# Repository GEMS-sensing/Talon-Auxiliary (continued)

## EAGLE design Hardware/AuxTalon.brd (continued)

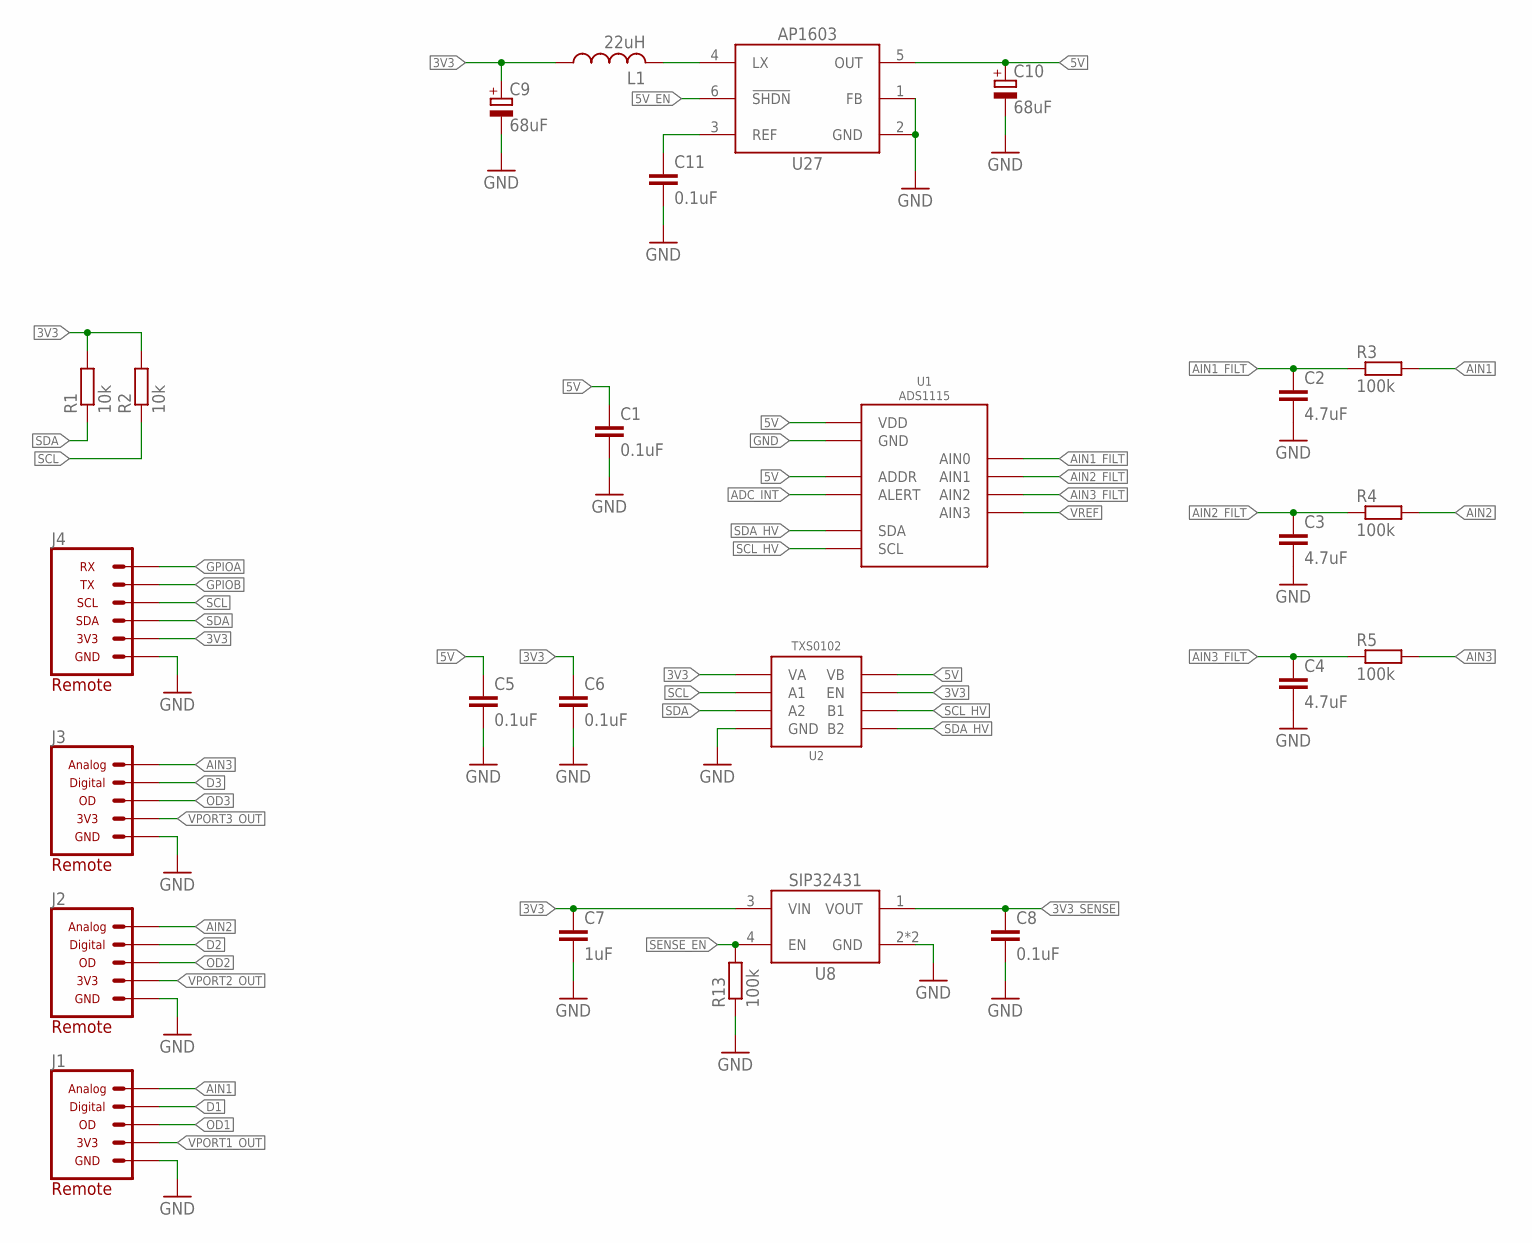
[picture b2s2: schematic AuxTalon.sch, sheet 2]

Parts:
C1, C5, C6, C8, C11: 0.1uF; C0402
C2, C3, C4: 4.7uF; C0805
C7: 1uF; C0603
C9, C10: 68uF; 153CLV-0605
J1, J2, J3: CONN_AUX_M12_REMOTE; 1X05_M12_TE_T41410
J4: CONN_TALON_REMOTE; 1X06_MICROLOCKPLUS
L1: 22uH; WE-TPC(3.8X3.8)
R1, R2: 10k; R0402
R3, R4, R5, R13: 100k; R0402
U1: ADS1115; VSSOP_10
U2: TXS0102DCU; DCU_(R-PDSO-G8)
U8: SIP32431TDFN; TDFN_4
U27: AP1603; TSOT23-6_DDC

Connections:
3V3: C6.1, C7.1, C9.+, J4.5 (3V3), L1.1, R1.2, R2.2, U2.3 (VA), U2.6 (EN), U8.3 (VIN); also elsewhere on the board
3V3_SENSE: C8.1, U8.1 (VOUT); also elsewhere on the board
5V: C1.1, C5.1, C10.+, U1.1 (ADDR), U1.8 (VDD), U2.7 (VB), U27.5 (OUT); also elsewhere on the board
5V_EN: U27.6 (!SHDN); also elsewhere on the board
ADC_INT: U1.2 (ALERT)
AIN1: J1.4 (ANALOG), R3.2
AIN1_FILT: C2.1, R3.1, U1.4 (AIN0)
AIN2: J2.4 (ANALOG), R4.2
AIN2_FILT: C3.1, R4.1, U1.5 (AIN1)
AIN3: J3.4 (ANALOG), R5.2
AIN3_FILT: C4.1, R5.1, U1.6 (AIN2)
D1: J1.5 (DIGITAL); also elsewhere on the board
D2: J2.5 (DIGITAL); also elsewhere on the board
D3: J3.5 (DIGITAL); also elsewhere on the board
GND: C1.2, C2.2, C3.2, C4.2, C5.2, C6.2, C7.2, C8.2, C9.-, C10.-, C11.2, J1.3 (GND), J2.3 (GND), J3.3 (GND), J4.6 (GND), R13.1, U1.3 (GND), U2.2 (GND), U8.2 (GND), U8.EP (GND), U27.1 (FB), U27.2 (GND); also elsewhere on the board
GPIOA: J4.1 (RX); also elsewhere on the board
GPIOB: J4.2 (TX); also elsewhere on the board
unnamed: C11.1, U27.3 (REF)
unnamed: L1.2, U27.4 (LX)
OD1: J1.2 (DIGITAL_OPENDRAIN); also elsewhere on the board
OD2: J2.2 (DIGITAL_OPENDRAIN); also elsewhere on the board
OD3: J3.2 (DIGITAL_OPENDRAIN); also elsewhere on the board
SCL: J4.3 (SCL), R2.1, U2.5 (A1); also elsewhere on the board
SCL_HV: U1.10 (SCL), U2.8 (B1)
SDA: J4.4 (SDA), R1.1, U2.4 (A2); also elsewhere on the board
SDA_HV: U1.9 (SDA), U2.1 (B2)
SENSE_EN: R13.2, U8.4 (EN); also elsewhere on the board
VPORT1_OUT: J1.1 (3V3); also elsewhere on the board
VPORT2_OUT: J2.1 (3V3); also elsewhere on the board
VPORT3_OUT: J3.1 (3V3); also elsewhere on the board
VREF: U1.7 (AIN3); also elsewhere on the board

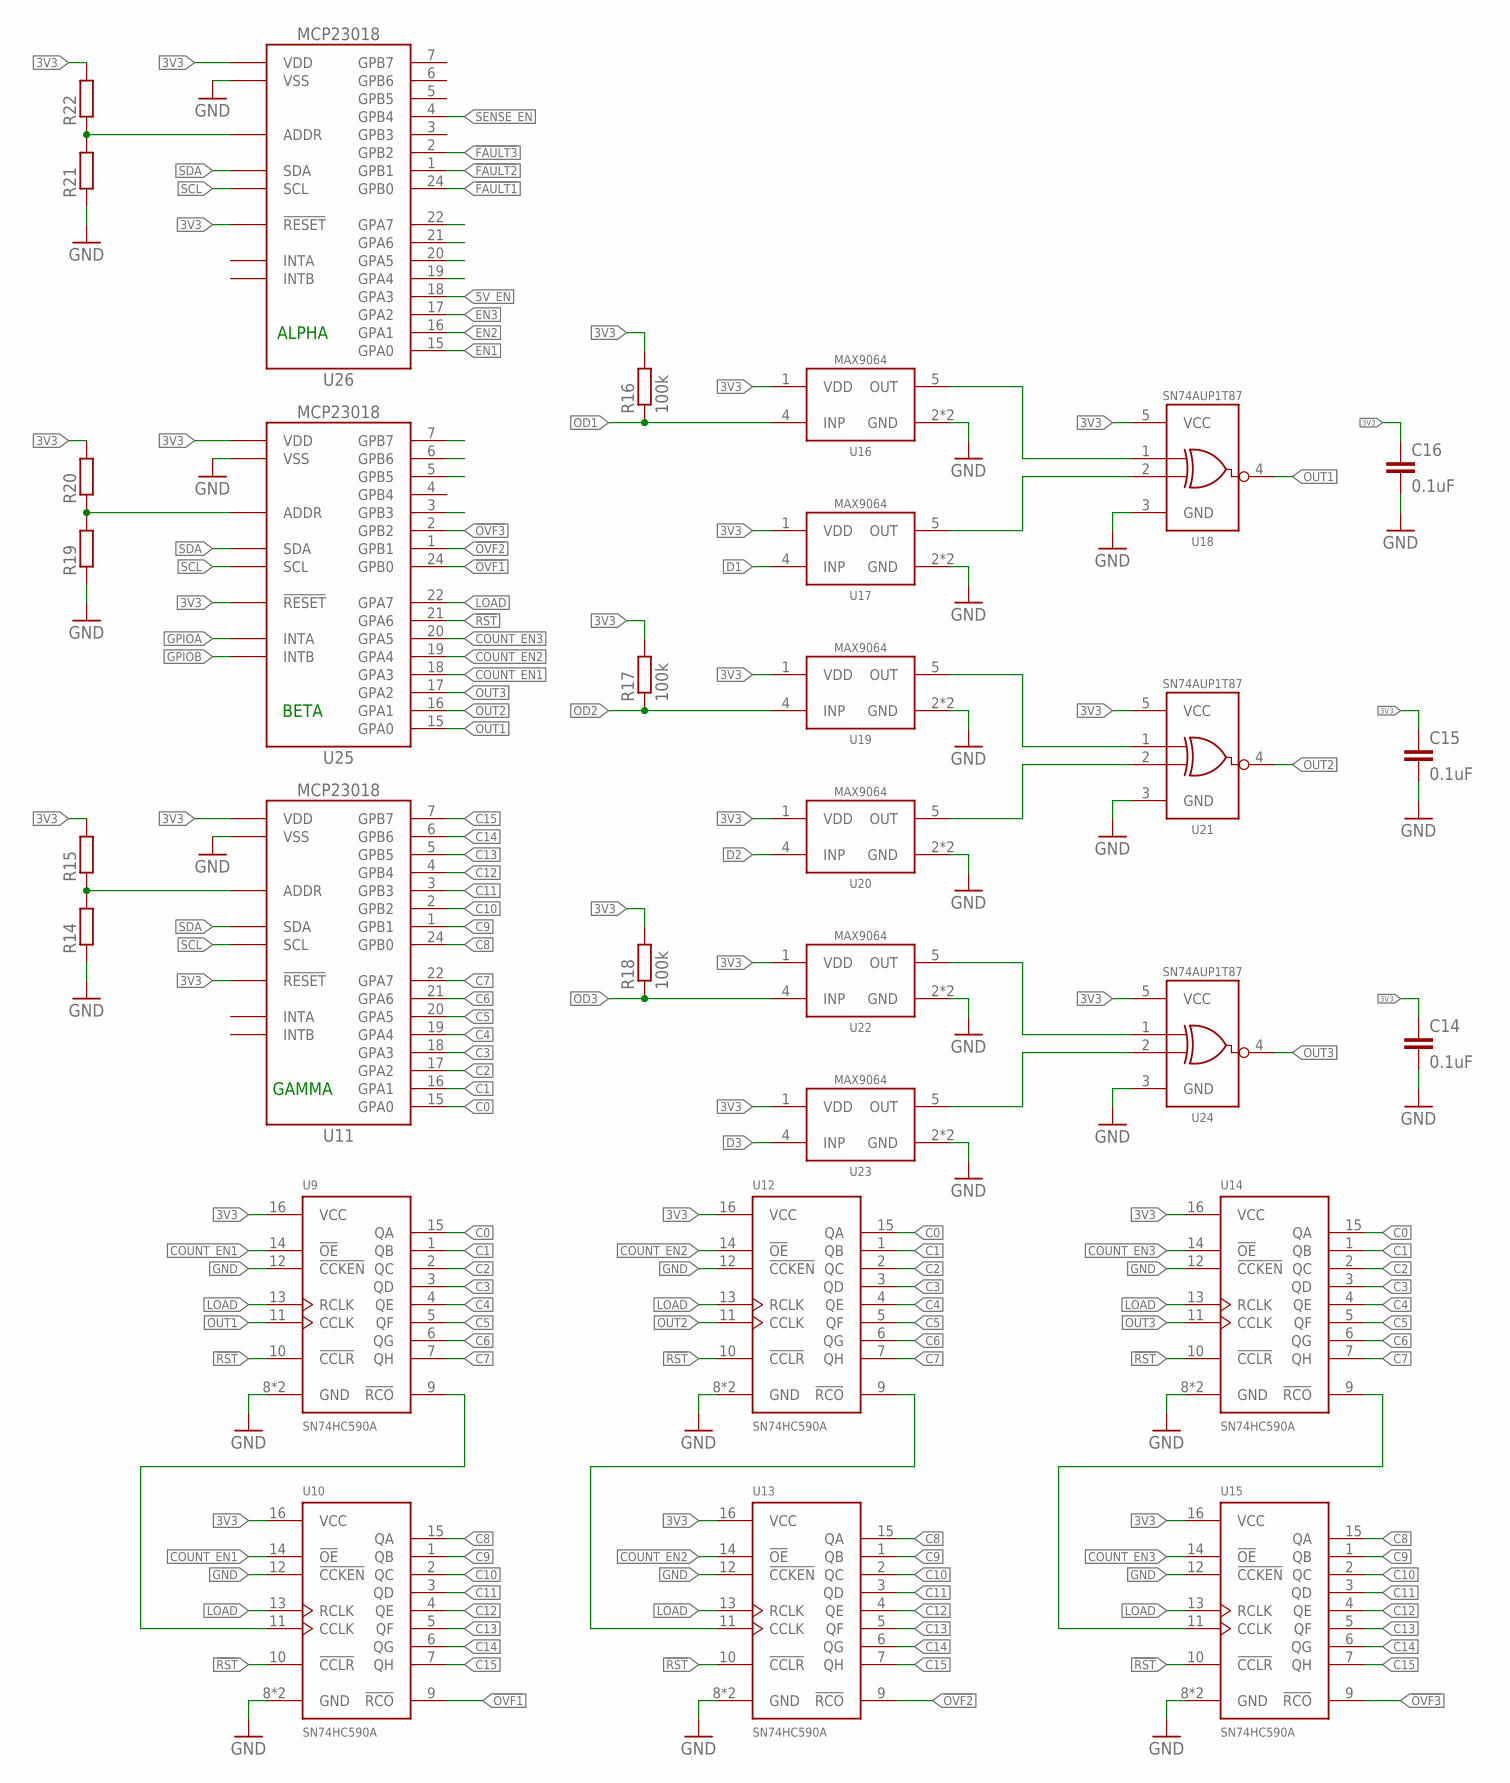
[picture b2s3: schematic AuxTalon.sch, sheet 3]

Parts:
C14, C15, C16: 0.1uF; C0402
R14, R15, R19, R20, R21, R22: R-EU_R0603; R0603
R16, R17, R18: 100k; R0402
U9, U10, U12, U13, U14, U15: SN74HC590AVQFN; VQFN-16
U11, U25, U26: MCP23018QFN; QFN24
U16, U17, U19, U20, U22, U23: MAX9064; SOT23-5
U18, U21, U24: SN74AUP1T87; DCK_R-PDSO-G5

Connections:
3V3: C14.1, C15.1, C16.1, R15.2, R16.2, R17.2, R18.2, R20.2, R22.2, U9.16 (VCC), U10.16 (VCC), U11.8 (VDD), U11.12 (!RESET), U12.16 (VCC), U13.16 (VCC), U14.16 (VCC), U15.16 (VCC), U16.1 (VDD), U17.1 (VDD), U18.5 (VCC), U19.1 (VDD), U20.1 (VDD), U21.5 (VCC), U22.1 (VDD), U23.1 (VDD), U24.5 (VCC), U25.8 (VDD), U25.12 (!RESET), U26.8 (VDD), U26.12 (!RESET); also elsewhere on the board
5V_EN: U26.18 (GPA3); also elsewhere on the board
!FAULT1: U26.24 (GPB0); also elsewhere on the board
!FAULT2: U26.1 (GPB1); also elsewhere on the board
!FAULT3: U26.2 (GPB2); also elsewhere on the board
!OVF1: U10.9 (!RCO), U25.24 (GPB0)
!OVF2: U13.9 (!RCO), U25.1 (GPB1)
!OVF3: U15.9 (!RCO), U25.2 (GPB2)
!RST: U9.10 (!CCLR), U10.10 (!CCLR), U12.10 (!CCLR), U13.10 (!CCLR), U14.10 (!CCLR), U15.10 (!CCLR), U25.21 (GPA6)
C0: U9.15 (QA), U11.15 (GPA0), U12.15 (QA), U14.15 (QA)
C1: U9.1 (QB), U11.16 (GPA1), U12.1 (QB), U14.1 (QB)
C2: U9.2 (QC), U11.17 (GPA2), U12.2 (QC), U14.2 (QC)
C3: U9.3 (QD), U11.18 (GPA3), U12.3 (QD), U14.3 (QD)
C4: U9.4 (QE), U11.19 (GPA4), U12.4 (QE), U14.4 (QE)
C5: U9.5 (QF), U11.20 (GPA5), U12.5 (QF), U14.5 (QF)
C6: U9.6 (QG), U11.21 (GPA6), U12.6 (QG), U14.6 (QG)
C7: U9.7 (QH), U11.22 (GPA7), U12.7 (QH), U14.7 (QH)
C8: U10.15 (QA), U11.24 (GPB0), U13.15 (QA), U15.15 (QA)
C9: U10.1 (QB), U11.1 (GPB1), U13.1 (QB), U15.1 (QB)
C10: U10.2 (QC), U11.2 (GPB2), U13.2 (QC), U15.2 (QC)
C11: U10.3 (QD), U11.3 (GPB3), U13.3 (QD), U15.3 (QD)
C12: U10.4 (QE), U11.4 (GPB4), U13.4 (QE), U15.4 (QE)
C13: U10.5 (QF), U11.5 (GPB5), U13.5 (QF), U15.5 (QF)
C14: U10.6 (QG), U11.6 (GPB6), U13.6 (QG), U15.6 (QG)
C15: U10.7 (QH), U11.7 (GPB7), U13.7 (QH), U15.7 (QH)
COUNT_EN1: U9.14 (!OE), U10.14 (!OE), U25.18 (GPA3)
COUNT_EN2: U12.14 (!OE), U13.14 (!OE), U25.19 (GPA4)
COUNT_EN3: U14.14 (!OE), U15.14 (!OE), U25.20 (GPA5)
D1: U17.4 (INP); also elsewhere on the board
D2: U20.4 (INP); also elsewhere on the board
D3: U23.4 (INP); also elsewhere on the board
EN1: U26.15 (GPA0); also elsewhere on the board
EN2: U26.16 (GPA1); also elsewhere on the board
EN3: U26.17 (GPA2); also elsewhere on the board
GND: C14.2, C15.2, C16.2, R14.1, R19.1, R21.1, U9.8 (GND), U9.12 (!CCKEN), U9.EP (GND), U10.8 (GND), U10.12 (!CCKEN), U10.EP (GND), U11.23 (VSS), U11.EP (VSS), U12.8 (GND), U12.12 (!CCKEN), U12.EP (GND), U13.8 (GND), U13.12 (!CCKEN), U13.EP (GND), U14.8 (GND), U14.12 (!CCKEN), U14.EP (GND), U15.8 (GND), U15.12 (!CCKEN), U15.EP (GND), U16.2 (GND), U16.3 (GND), U17.2 (GND), U17.3 (GND), U18.3 (GND), U19.2 (GND), U19.3 (GND), U20.2 (GND), U20.3 (GND), U21.3 (GND), U22.2 (GND), U22.3 (GND), U23.2 (GND), U23.3 (GND), U24.3 (GND), U25.23 (VSS), U25.EP (VSS), U26.23 (VSS), U26.EP (VSS); also elsewhere on the board
GPIOA: U25.14 (INTA); also elsewhere on the board
GPIOB: U25.13 (INTB); also elsewhere on the board
LOAD: U9.13 (RCLK), U10.13 (RCLK), U12.13 (RCLK), U13.13 (RCLK), U14.13 (RCLK), U15.13 (RCLK), U25.22 (GPA7)
MUX_SEL2: U25.5 (GPB5); also elsewhere on the board
unnamed: U9.9 (!RCO), U10.11 (CCLK)
unnamed: U12.9 (!RCO), U13.11 (CCLK)
unnamed: U14.9 (!RCO), U15.11 (CCLK)
unnamed: R14.2, R15.1, U11.11 (ADDR)
unnamed: U20.5 (OUT), U21.2 (B)
unnamed: U19.5 (OUT), U21.1 (A)
unnamed: U16.5 (OUT), U18.1 (A)
unnamed: U17.5 (OUT), U18.2 (B)
unnamed: U23.5 (OUT), U24.2 (B)
unnamed: U22.5 (OUT), U24.1 (A)
unnamed: R21.2, R22.1, U26.11 (ADDR)
unnamed: R19.2, R20.1, U25.11 (ADDR)
OD1: R16.1, U16.4 (INP); also elsewhere on the board
OD2: R17.1, U19.4 (INP); also elsewhere on the board
OD3: R18.1, U22.4 (INP); also elsewhere on the board
OUT1: U9.11 (CCLK), U18.4 (Y), U25.15 (GPA0)
OUT2: U12.11 (CCLK), U21.4 (Y), U25.16 (GPA1)
OUT3: U14.11 (CCLK), U24.4 (Y), U25.17 (GPA2)
SCL: U11.9 (SCL), U25.9 (SCL), U26.9 (SCL); also elsewhere on the board
SDA: U11.10 (SDA), U25.10 (SDA), U26.10 (SDA); also elsewhere on the board
SENSE_EN: U26.4 (GPB4); also elsewhere on the board

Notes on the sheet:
BETA
GAMMA
ALPHA

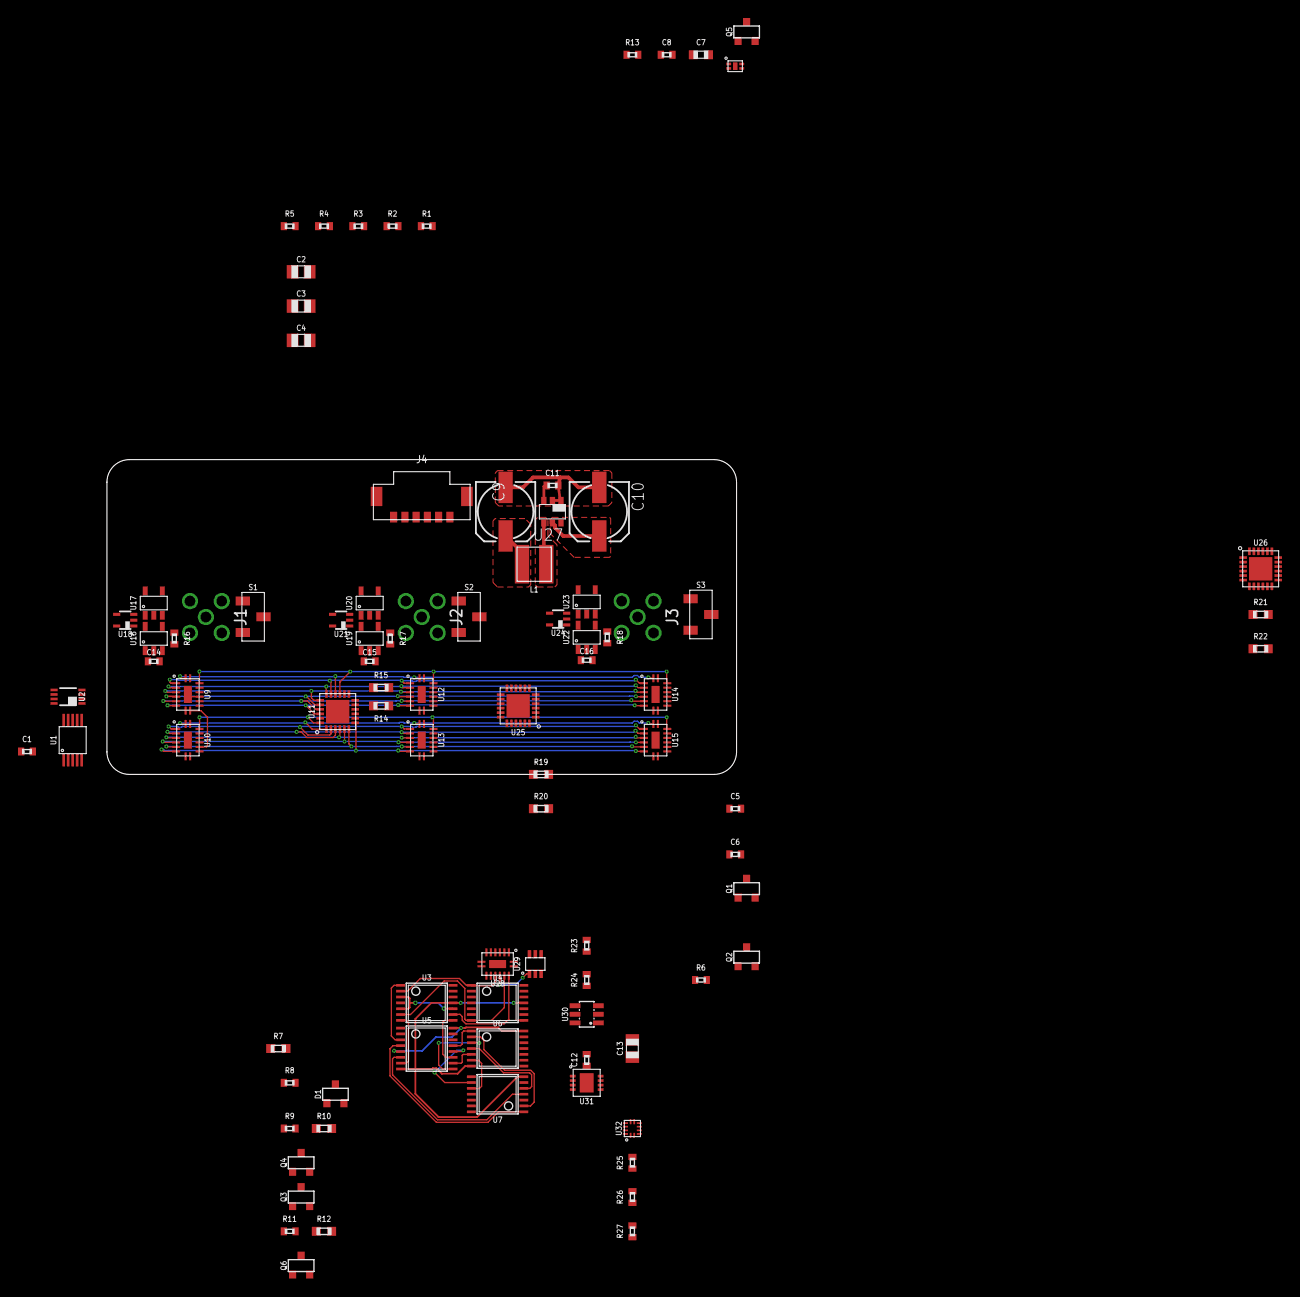
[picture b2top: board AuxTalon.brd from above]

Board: 2 copper layers, 70.0 x 35.0 mm, 90 parts (0 on the bottom side), 107 nets.

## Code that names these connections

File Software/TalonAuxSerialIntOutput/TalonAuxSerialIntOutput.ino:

#include <Wire.h>
#include <Arduino.h>
#include <MCP23018.h>

// #define OVERFLOW_ONLY 

//Input Pins
const uint8_t GPIOA = 5;
const uint8_t GPIOB = 6;

//IO Expander Pins - ALPHA
const uint8_t REG_EN = 7;
const uint8_t ADC_INT = 6;

//IO Expander Pins - BETA
const uint8_t LOAD = 7;
const uint8_t RST = 6;
const uint8_t OUT1 = 0;
// const uint8_t COUNT_EN3 = 5;
// const uint8_t COUNT_EN2 = 4;
const uint8_t COUNT_EN1 = 3;
const uint8_t OVF1 = 8;

//Configured for pins on the Particle Boron
//const uint8_t EXT_EN = 8;
//const uint8_t SDA_CTRL = 2;

const uint8_t EXT_EN = 13;
const uint8_t SDA_CTRL = 5;

volatile bool OverflowFlags[3] = {0}; //Set by OverflowISR, cleared in main loop
volatile bool EventFlags[3] = {0}; //Set by EventISR, cleared in main loop

volatile bool NewOverflow = false; //Used to indicate a new overflow condition
volatile bool NewEvent = false; //Used to indicate a new event condition

char ReadArray[25] = {0};

MCP23018 ioAlpha(0x23); //FIX! RETURN to 0x20
MCP23018 ioBeta(0x20); //FIX! RETURN to 0x23
MCP23018 ioGamma(0x24);


void setup() {

	// pinMode(EXT_EN, OUTPUT); 
	// digitalWrite(EXT_EN, HIGH);
	Serial.begin(115200);
	// delay(5000);
	// pinMode(SDA_CTRL, OUTPUT);
	// digitalWrite(SDA_CTRL, LOW);
	// delay(5000);
	ioAlpha.begin();
	ioBeta.begin();
	ioGamma.begin();
	// Wire.begin();
 //DEBUG1!
	SetDefaultPins(); //Set the default configuration for sensing 
	attachInterrupt(digitalPinToInterrupt(GPIOA), EventISR, FALLING); //Setup interrupt for GPIOA
	attachInterrupt(digitalPinToInterrupt(GPIOB), OverflowISR, FALLING); //Setup interrupt for GPIOA
	delay(1000);

	Serial.println("Begin Aux Demo...");
}

void loop() {
	while(1) {
		if(NewOverflow) {
			Serial.print("OVERFLOW:\t");
			for(int i = 0; i < 3; i++) { //Find more elegant solution??
				Serial.print(OverflowFlags[i]);
				Serial.print("\t");
				OverflowFlags[i] = 0; //clear flag once printed out
			}
			Serial.print("\n");
			NewOverflow = false; //Clear indicator flag once done printing
		}

		#if !defined(OVERFLOW_ONLY) //Don't print out all the pulses if we only want to look at overflow events
			if(NewEvent) {
				Serial.print("EVENT:\t");
				for(int i = 0; i < 3; i++) { //Find more elegant solution??
					Serial.print(EventFlags[i]);
					Serial.print("\t");
					EventFlags[i] = 0; //clear flag once printed out
				}
				Serial.print("\n");
				NewEvent = false; //Clear indicator flag once done printing
			}
		#endif
	}
}

void SetDefaultPins()
{
	for(int i = 0; i < 16; i++) { //Set all Gamma pins to input
		ioGamma.pinMode(i, INPUT);
	} 

	for(int i = 0; i < 3; i++) { //Set each group of IO pins seperately
		ioBeta.pinMode(OUT1 + i, INPUT); //Set all outputs from counters as inputs to I/O expander
		ioBeta.pinMode(COUNT_EN1 + i, OUTPUT); //Set enable control as output
		ioBeta.pinMode(OVF1 + i, INPUT); //Set overflow pins as inputs
		ioBeta.digitalWrite(COUNT_EN1 + 1, HIGH); //Default to enable all counters
		ioBeta.setIntPinConfig(OVF1 + i, false, 1); //Set overflow pins to trigger an interrupt whenever they are low
		ioBeta.setIntPinConfig(OUT1 + i, true); //Set output pins to trigger an interrupt anytime they change from the previous value
		ioBeta.setInterrupt(OVF1 + i, true); //Turn on interrupt for overflow pins
		ioBeta.setInterrupt(OUT1 + i, true); //Turn on interrupt for output pins
	}
	ioBeta.pinMode(LOAD, OUTPUT);
	ioBeta.pinMode(RST, OUTPUT);
	ioBeta.digitalWrite(LOAD, LOW); //Start with load in low position, will load on high going edge
	ioBeta.digitalWrite(RST, HIGH); //Negate reset by default

	ioAlpha.pinMode(REG_EN, OUTPUT);
	ioAlpha.digitalWrite(REG_EN, HIGH); //Default 5V to on
	ioAlpha.pinMode(ADC_INT, INPUT_PULLUP); //Setup ADC int as an input pullup for the open drain
	ioBeta.clearInterrupt(BOTH); //Make sure there are no pending interrupts 
}


uint16_t ReadCounters(uint8_t Port, bool NewRead) //Pass in which counter to read
{
	// static uint16_t Count1 = 0; //Keep all counters as local statics to be returned at request
	// static uint16_t Count2 = 0;
	// static uint16_t Count3 = 0; 

	static uint16_t Count[3] = {0}; //Keep all counters as local statics to be returned at request 

	if(NewRead) {
		ioBeta.digitalWrite(LOAD, HIGH); //Load all values
		delayMicroseconds(1); //Delay min number of microseconds to ensure a pulse
		ioBeta.digitalWrite(LOAD, LOW);

		for(int i = 0; i < 3; i++) { //Get count n
			ioBeta.digitalWrite(COUNT_EN1 + i, HIGH); //Turn on outputs of counter n 
			Count[i] = ioGamma.readBus(); //Grab bus
			ioBeta.digitalWrite(COUNT_EN1 + i, LOW); //Turn off outputs of countern
		}

		// ioBeta.digitalWrite(COUNT_EN1, HIGH); //Get count 1
		// Count1 = ioGamma.readWord();
		// ioBeta.digitalWrite(COUNT_EN1, LOW);

		// ioBeta.digitalWrite(COUNT_EN2, HIGH); //Get count 2
		// Count2 = ioGamma.readWord();
		// ioBeta.digitalWrite(COUNT_EN2, LOW);

		// ioBeta.digitalWrite(COUNT_EN3, HIGH); //Get count 3
		// Count3 = ioGamma.readWord();
		// ioBeta.digitalWrite(COUNT_EN3, LOW);
	}

	return Count[Port]; //Return the desired 16 bit count
}

void ClearCounters() //Clear all counters
{
	ioBeta.digitalWrite(RST, LOW);
	// ASM('NOP'); //Delay minimal time, needs only to be longer than 200ns, can likely eliminate delay
	delayMicroseconds(1); //Delay min number of microseconds to ensure a pulse
	ioBeta.digitalWrite(RST, HIGH);
}

void EventISR()
{
	NewEvent = true; //Set indicator flag
	for(int i = 0; i < 3; i++) {
		EventFlags[i] = ioBeta.getInterrupt(OUT1 + i); //Grab each interrupt flag
	}
	// EventFlags[0] = ioBeta.getInterrupt(OUT1); //DEBUG!
	ioBeta.clearInterrupt(A); //Clear interrupt A
}

void OverflowISR()
{
	NewOverflow = true; //Set indicator flag
	for(int i = 0; i < 3; i++) {
		OverflowFlags[i] = ioBeta.getInterrupt(OVF1 + i); //Grab each interrupt flag
	}
	ioBeta.clearInterrupt(B); //Clear interrupt B
}

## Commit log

2021-09-23 Prelim Schematic Capture
    About 90% done with schematic capture
2021-10-07 Preliminary work done on AuxTalon
2021-10-07 Preliminary copper layout done on Load Switch Aux Talon
    Switched to Aux Talon using self contained load switches in order to reduce layout size. Preliminary copper layout done, addition of ESD diodes and review still required.
2021-10-07 Added ESD diodes, moved connector positioning
    Added some ESD diodes on signal lines and changed positioning of connectors to restrict install to a single direction
2021-10-12 Layout, gerbers, and BoM for v0.0 - sent to fab
2021-10-14 v0.1 Updates - Added EEPROM
    Added EEPROM to board
2021-10-14 Generated documentation for v0.1 quote
2021-10-22 Added serial firmware demos
    Added demo for reading of counters and general serial control, also added demo for testing interrupt interfacing
2021-11-23 v1.0 Updates
    Added voltage sensing for ports, swapped 5V converter, sent v1.0 to fab
2021-11-23 Minor updates to demo code
2021-12-08 Updated solder paste
2021-12-10 v1.1 update
    Moved via
2022-02-11 Prelim v1.3 updates
2022-02-13 v1.3 Layout
2022-03-30 Added license
2022-04-06 Updated part vals for v1.3
2022-04-06 Updates for modified BoM
2022-04-25 v1.4 Updates
    Updated schematic and layout, boards sent to fab
2023-05-15 Production files for v1.4
2023-05-15 Updates for v1.5
    - Changed load switch
2023-07-07 Changed Cout value
    Changed `C13`, `C18`, `C20` from 1uF to 10uF
2024-09-01 Updated README and board images
2024-11-01 Updated README to include pinouts
